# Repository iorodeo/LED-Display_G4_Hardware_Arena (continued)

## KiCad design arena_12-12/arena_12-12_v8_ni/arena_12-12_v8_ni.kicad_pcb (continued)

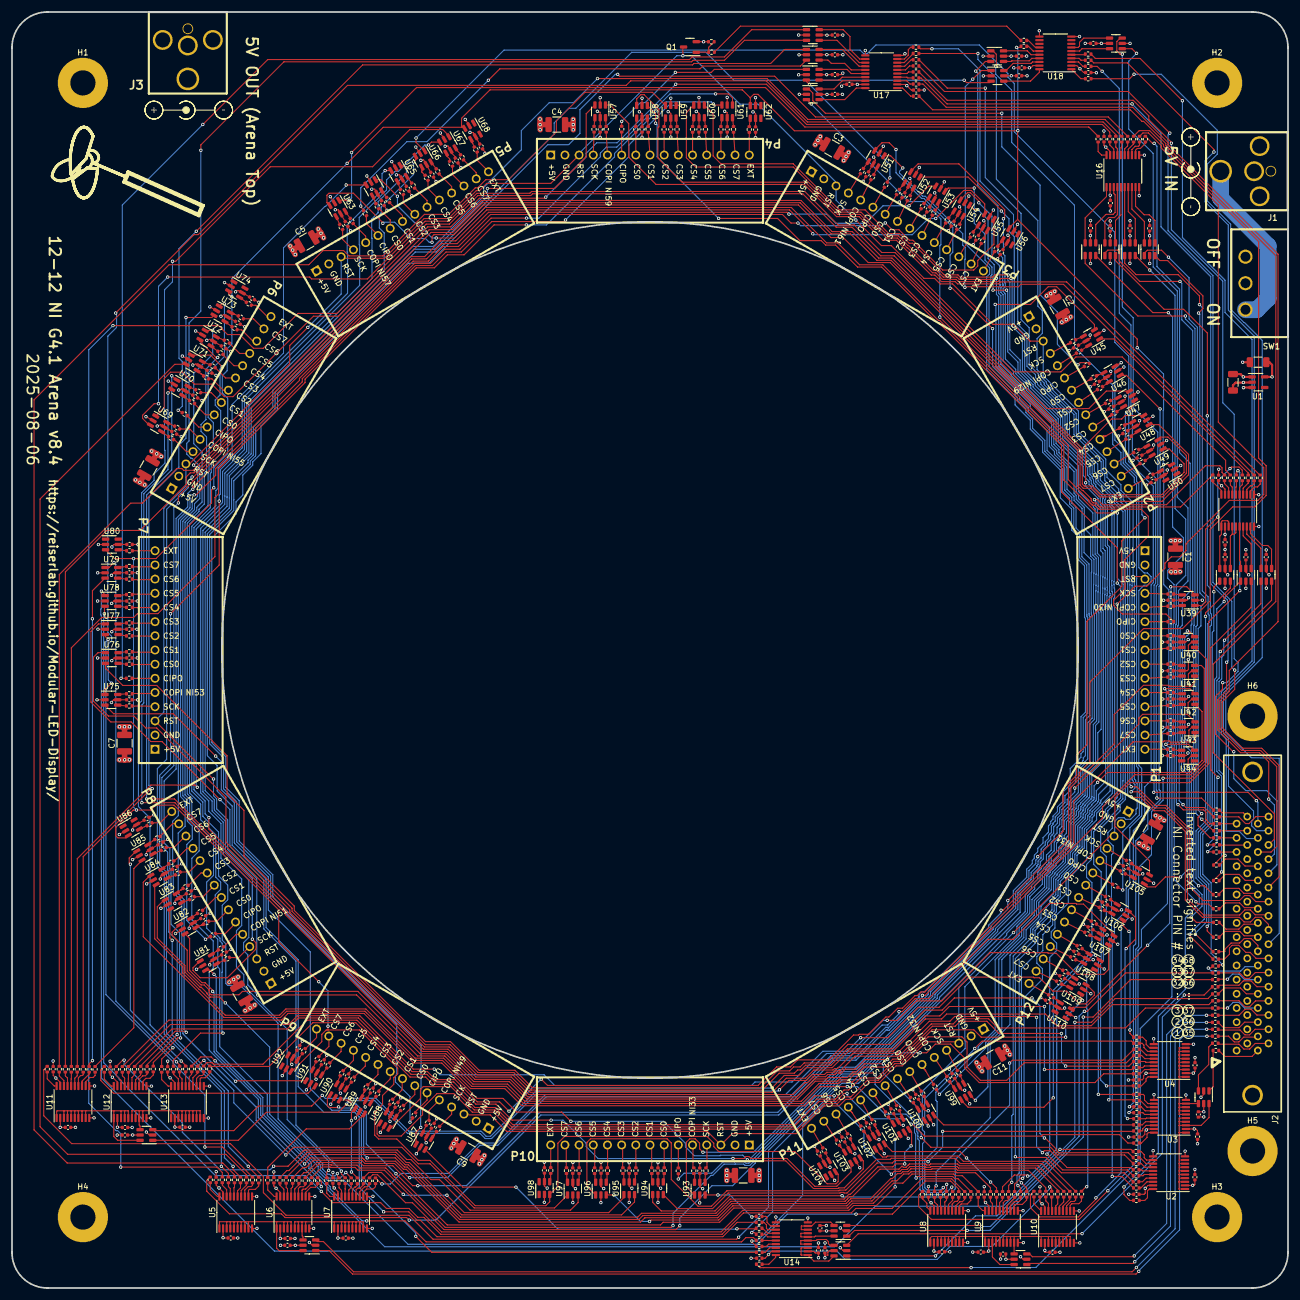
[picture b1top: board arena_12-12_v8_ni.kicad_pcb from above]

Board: 6 copper layers, 228.6 x 228.6 mm, 581 parts (0 on the bottom side), 658 nets.

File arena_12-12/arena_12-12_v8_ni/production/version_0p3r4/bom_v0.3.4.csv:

Designator,Footprint,Quantity,Value,LCSC Part #
"C1, C10, C11, C12, C2, C3, C4, C5, C6, C7, C8, C9",1210,12,100uF,C7432790
"C100, C101, C102, C103, C104, C105, C106, C107, C108, C109, C110, C111, C112, C113, C114, C115, C116, C117, C118, C119, C120, C121, C122, C123, C124, C125, C126, C127, C128, C129, C130, C131, C132, C133, C134, C135, C136, C137, C138, C139, C140, C15, C16, C17, C18, C19, C20, C21, C22, C23, C24, C25, C26, C27, C28, C29, C30, C31, C32, C33, C34, C35, C36, C37, C38, C39, C40, C41, C42, C43, C44, C45, C46, C47, C48, C49, C50, C51, C52, C53, C54, C55, C56, C57, C58, C59, C60, C61, C62, C63, C64, C65, C66, C67, C68, C69, C70, C71, C72, C73, C74, C75, C76, C77, C78, C79, C80, C81, C82, C83, C84, C85, C86, C87, C88, C89, C90, C91, C92, C93, C94, C95, C96, C97, C98, C99",0402,126,0.1uF,C1525
"C13, C14",1206,2,10uF,C342827
"J1, J3",DCJACK_2PIN_HIGHCURRENT,2,Barrel_Jack,C2928097
J2,TE_CONN_DSUB_VERT_68,1,NI_TE_68pos,C5172587
"P1, P10, P11, P12, P2, P3, P4, P5, P6, P7, P8, P9",HEADER_TOP,12,CONN15,C18078136
Q1,SOT-23-3,1,MOSFET_NCHAN,C165220
"R1, R10, R100, R101, R102, R103, R104, R105, R106, R107, R108, R109, R11, R110, R111, R112, R113, R114, R115, R116, R117, R118, R119, R12, R120, R121, R122, R123, R124, R125, R126, R127, R128, R129, R13, R130, R131, R132, R133, R134, R135, R136, R137, R138, R139, R14, R140, R141, R142, R143, R144, R145, R146, R147, R148, R149, R15, R150, R151, R152, R153, R154, R155, R156, R157, R158, R159, R16, R160, R161, R162, R163, R164, R165, R166, R167, R168, R169, R17, R170, R171, R172, R173, R174, R175, R176, R177, R178, R179, R18, R180, R181, R182, R183, R184, R185, R186, R187, R188, R189, R19, R190, R191, R192, R193, R194, R195, R196, R197, R198, R199, R2, R20, R200, R201, R202, R203, R204, R205, R206, R207, R208, R209, R21, R210, R211, R212, R213, R214, R215, R216, R217, R218, R219, R22, R220, R221, R222, R223, R224, R225, R226, R227, R228, R229, R23, R230, R231, R232, R233, R234, R235, R236, R237, R238, R239, R24, R240, R241, R242, R243, R244, R245, R246, R247, R248, R249, R25, R250, R251, R252, R253, R254, R255, R256, R257, R258, R259, R26, R260, R261, R262, R263, R264, R265, R266, R267, R268, R269, R27, R270, R271, R272, R273, R274, R275, R276, R277, R278, R279",0402,200,33,C25105
"R28, R280, R281, R282, R283, R284, R285, R286, R287, R288, R289, R29, R290, R291, R292, R293, R294, R295, R296, R297, R298, R299, R3, R30, R300, R301, R302, R303, R304, R305, R306, R31, R32, R33, R34, R35, R36, R37, R38, R39, R4, R40, R41, R42, R43, R44, R45, R46, R47, R48, R49, R5, R50, R51, R52, R53, R54, R55, R56, R57, R58, R59, R6, R60, R61, R62, R63, R64, R65, R66, R67, R68, R69, R7, R70, R71, R72, R73, R74, R75, R76, R77, R78, R79, R8, R80, R81, R82, R83, R84, R85, R86, R87, R88, R89, R9, R90, R91, R92, R93, R94, R95, R96, R97, R98, R99",0402,106,33,C25105
R307,0402,1,20k,C25765
R308,0402,1,200,C25087
SW1,slide_switch,1,SW_SPDT,C2798743
U1,SOT-23-5,1,AP2112K-3.3,C51118
"U10, U11, U12, U13, U14, U15, U16, U17, U18, U2, U3, U4, U5, U6, U7, U8, U9",TSSOP-20_4.4x6.5mm_P0.65mm,17,TXB0108PW,C53406
"U100, U101, U102, U103, U104, U105, U106, U107, U108, U109, U110, U19, U20, U21, U22, U23, U24, U25, U26, U27, U28, U29, U30, U31, U32, U33, U34, U35, U36, U37, U38, U39, U40, U41, U42, U43, U44, U45, U46, U47, U48, U49, U50, U51, U52, U53, U54, U55, U56, U57, U58, U59, U60, U61, U62, U63, U64, U65, U66, U67, U68, U69, U70, U71, U72, U73, U74, U75, U76, U77, U78, U79, U80, U81, U82, U83, U84, U85, U86, U87, U88, U89, U90, U91, U92, U93, U94, U95, U96, U97, U98, U99",SOT-23-6,92,74LVC2G17,C10429

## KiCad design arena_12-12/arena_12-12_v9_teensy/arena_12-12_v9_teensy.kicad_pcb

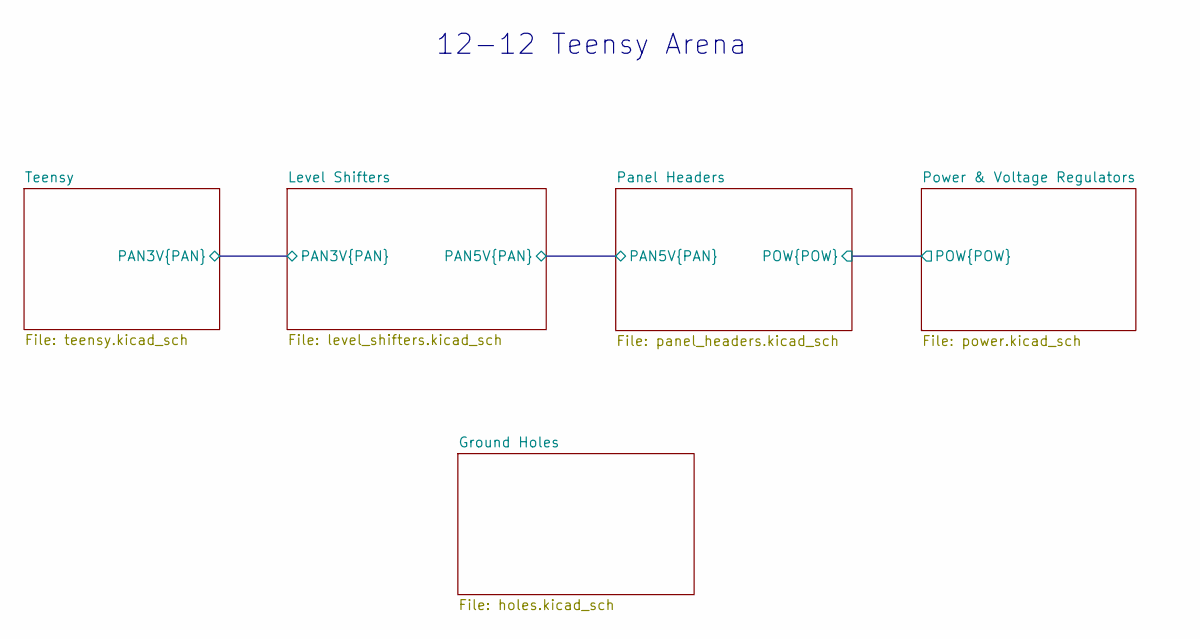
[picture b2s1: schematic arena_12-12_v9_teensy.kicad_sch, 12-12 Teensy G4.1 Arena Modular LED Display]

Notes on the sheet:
12-12 Teensy Arena

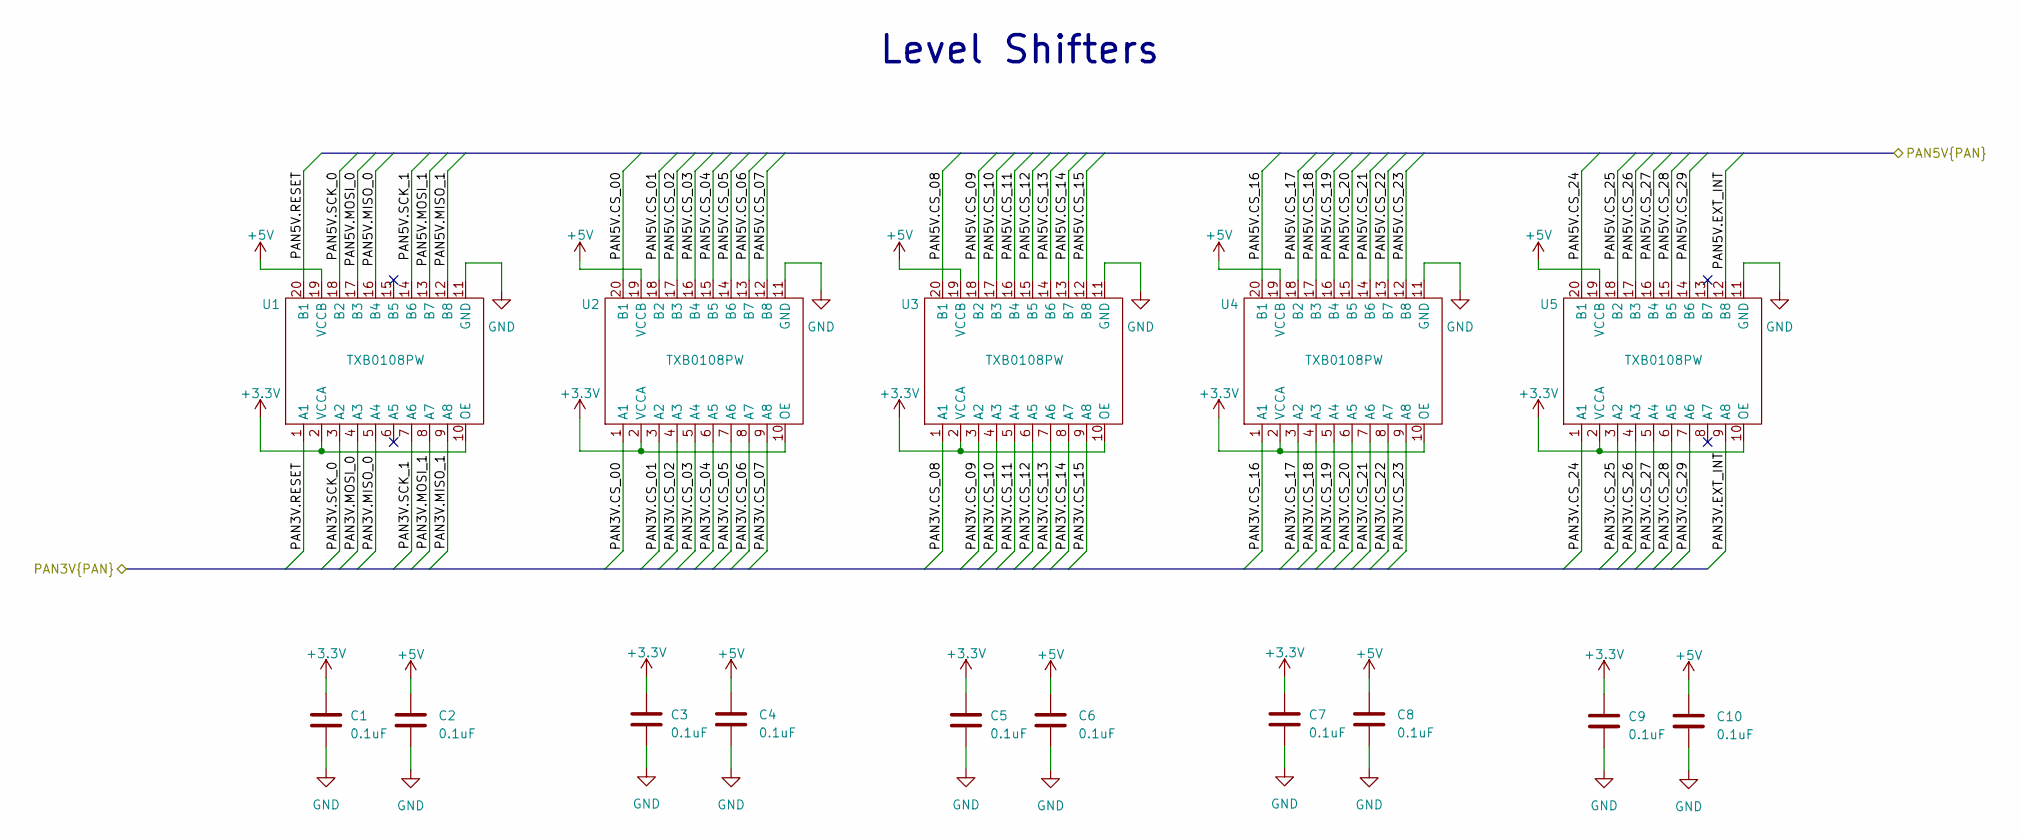
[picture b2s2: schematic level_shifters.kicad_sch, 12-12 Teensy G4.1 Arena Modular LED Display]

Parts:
C1, C2, C3, C4, C5, C6, C7, C8, C9, C10: 0.1uF; C_0603_1608Metric; MPN CL10B104KB8NNNC; DigiKey PN 1276-1000-2-ND
U1, U2, U3, U4, U5: TXB0108PW; TSSOP-20_4.4x6.5mm_P0.65mm; MPN TXB0108PWR; DigiKey PN 296-21527-2-ND

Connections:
+3.3V: C1.1, C3.1, C5.1, C7.1, C9.1, U1.2 (VCCA), U1.10 (OE), U2.2 (VCCA), U2.10 (OE), U3.2 (VCCA), U3.10 (OE), U4.2 (VCCA), U4.10 (OE), U5.2 (VCCA), U5.10 (OE); also elsewhere on the board
+5V: C2.1, C4.1, C6.1, C8.1, C10.1, U1.19 (VCCB), U2.19 (VCCB), U3.19 (VCCB), U4.19 (VCCB), U5.19 (VCCB); also elsewhere on the board
/Level Shifters/PAN3V.CS_00: U2.1 (A1); also elsewhere on the board
/Level Shifters/PAN3V.CS_01: U2.3 (A2); also elsewhere on the board
/Level Shifters/PAN3V.CS_02: U2.4 (A3); also elsewhere on the board
/Level Shifters/PAN3V.CS_03: U2.5 (A4); also elsewhere on the board
/Level Shifters/PAN3V.CS_04: U2.6 (A5); also elsewhere on the board
/Level Shifters/PAN3V.CS_05: U2.7 (A6); also elsewhere on the board
/Level Shifters/PAN3V.CS_06: U2.8 (A7); also elsewhere on the board
/Level Shifters/PAN3V.CS_07: U2.9 (A8); also elsewhere on the board
/Level Shifters/PAN3V.CS_08: U3.1 (A1); also elsewhere on the board
/Level Shifters/PAN3V.CS_09: U3.3 (A2); also elsewhere on the board
/Level Shifters/PAN3V.CS_10: U3.4 (A3); also elsewhere on the board
/Level Shifters/PAN3V.CS_11: U3.5 (A4); also elsewhere on the board
/Level Shifters/PAN3V.CS_12: U3.6 (A5); also elsewhere on the board
/Level Shifters/PAN3V.CS_13: U3.7 (A6); also elsewhere on the board
/Level Shifters/PAN3V.CS_14: U3.8 (A7); also elsewhere on the board
/Level Shifters/PAN3V.CS_15: U3.9 (A8); also elsewhere on the board
/Level Shifters/PAN3V.CS_16: U4.1 (A1); also elsewhere on the board
/Level Shifters/PAN3V.CS_17: U4.3 (A2); also elsewhere on the board
/Level Shifters/PAN3V.CS_18: U4.4 (A3); also elsewhere on the board
/Level Shifters/PAN3V.CS_19: U4.5 (A4); also elsewhere on the board
/Level Shifters/PAN3V.CS_20: U4.6 (A5); also elsewhere on the board
/Level Shifters/PAN3V.CS_21: U4.7 (A6); also elsewhere on the board
/Level Shifters/PAN3V.CS_22: U4.8 (A7); also elsewhere on the board
/Level Shifters/PAN3V.CS_23: U4.9 (A8); also elsewhere on the board
/Level Shifters/PAN3V.CS_24: U5.1 (A1); also elsewhere on the board
/Level Shifters/PAN3V.CS_25: U5.3 (A2); also elsewhere on the board
/Level Shifters/PAN3V.CS_26: U5.4 (A3); also elsewhere on the board
/Level Shifters/PAN3V.CS_27: U5.5 (A4); also elsewhere on the board
/Level Shifters/PAN3V.CS_28: U5.6 (A5); also elsewhere on the board
/Level Shifters/PAN3V.CS_29: U5.7 (A6); also elsewhere on the board
/Level Shifters/PAN3V.EXT_INT: U5.9 (A8); also elsewhere on the board
/Level Shifters/PAN3V.MISO_0: U1.5 (A4); also elsewhere on the board
/Level Shifters/PAN3V.MISO_1: U1.9 (A8); also elsewhere on the board
/Level Shifters/PAN3V.MOSI_0: U1.4 (A3); also elsewhere on the board
/Level Shifters/PAN3V.MOSI_1: U1.8 (A7); also elsewhere on the board
/Level Shifters/PAN3V.RESET: U1.1 (A1); also elsewhere on the board
/Level Shifters/PAN3V.SCK_0: U1.3 (A2); also elsewhere on the board
/Level Shifters/PAN3V.SCK_1: U1.7 (A6); also elsewhere on the board
/Level Shifters/PAN5V.CS_00: U2.20 (B1); also elsewhere on the board
/Level Shifters/PAN5V.CS_01: U2.18 (B2); also elsewhere on the board
/Level Shifters/PAN5V.CS_02: U2.17 (B3); also elsewhere on the board
/Level Shifters/PAN5V.CS_03: U2.16 (B4); also elsewhere on the board
/Level Shifters/PAN5V.CS_04: U2.15 (B5); also elsewhere on the board
/Level Shifters/PAN5V.CS_05: U2.14 (B6); also elsewhere on the board
/Level Shifters/PAN5V.CS_06: U2.13 (B7); also elsewhere on the board
/Level Shifters/PAN5V.CS_07: U2.12 (B8); also elsewhere on the board
/Level Shifters/PAN5V.CS_08: U3.20 (B1); also elsewhere on the board
/Level Shifters/PAN5V.CS_09: U3.18 (B2); also elsewhere on the board
/Level Shifters/PAN5V.CS_10: U3.17 (B3); also elsewhere on the board
/Level Shifters/PAN5V.CS_11: U3.16 (B4); also elsewhere on the board
/Level Shifters/PAN5V.CS_12: U3.15 (B5); also elsewhere on the board
/Level Shifters/PAN5V.CS_13: U3.14 (B6); also elsewhere on the board
/Level Shifters/PAN5V.CS_14: U3.13 (B7); also elsewhere on the board
/Level Shifters/PAN5V.CS_15: U3.12 (B8); also elsewhere on the board
/Level Shifters/PAN5V.CS_16: U4.20 (B1); also elsewhere on the board
/Level Shifters/PAN5V.CS_17: U4.18 (B2); also elsewhere on the board
/Level Shifters/PAN5V.CS_18: U4.17 (B3); also elsewhere on the board
/Level Shifters/PAN5V.CS_19: U4.16 (B4); also elsewhere on the board
/Level Shifters/PAN5V.CS_20: U4.15 (B5); also elsewhere on the board
/Level Shifters/PAN5V.CS_21: U4.14 (B6); also elsewhere on the board
/Level Shifters/PAN5V.CS_22: U4.13 (B7); also elsewhere on the board
/Level Shifters/PAN5V.CS_23: U4.12 (B8); also elsewhere on the board
/Level Shifters/PAN5V.CS_24: U5.20 (B1); also elsewhere on the board
/Level Shifters/PAN5V.CS_25: U5.18 (B2); also elsewhere on the board
/Level Shifters/PAN5V.CS_26: U5.17 (B3); also elsewhere on the board
/Level Shifters/PAN5V.CS_27: U5.16 (B4); also elsewhere on the board
/Level Shifters/PAN5V.CS_28: U5.15 (B5); also elsewhere on the board
/Level Shifters/PAN5V.CS_29: U5.14 (B6); also elsewhere on the board
/Level Shifters/PAN5V.EXT_INT: U5.12 (B8); also elsewhere on the board
/Level Shifters/PAN5V.MISO_0: U1.16 (B4); also elsewhere on the board
/Level Shifters/PAN5V.MISO_1: U1.12 (B8); also elsewhere on the board
/Level Shifters/PAN5V.MOSI_0: U1.17 (B3); also elsewhere on the board
/Level Shifters/PAN5V.MOSI_1: U1.13 (B7); also elsewhere on the board
/Level Shifters/PAN5V.RESET: U1.20 (B1); also elsewhere on the board
/Level Shifters/PAN5V.SCK_0: U1.18 (B2); also elsewhere on the board
/Level Shifters/PAN5V.SCK_1: U1.14 (B6); also elsewhere on the board
GND: C1.2, C2.2, C3.2, C4.2, C5.2, C6.2, C7.2, C8.2, C9.2, C10.2, U1.11 (GND), U2.11 (GND), U3.11 (GND), U4.11 (GND), U5.11 (GND); also elsewhere on the board

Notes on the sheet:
Level Shifters

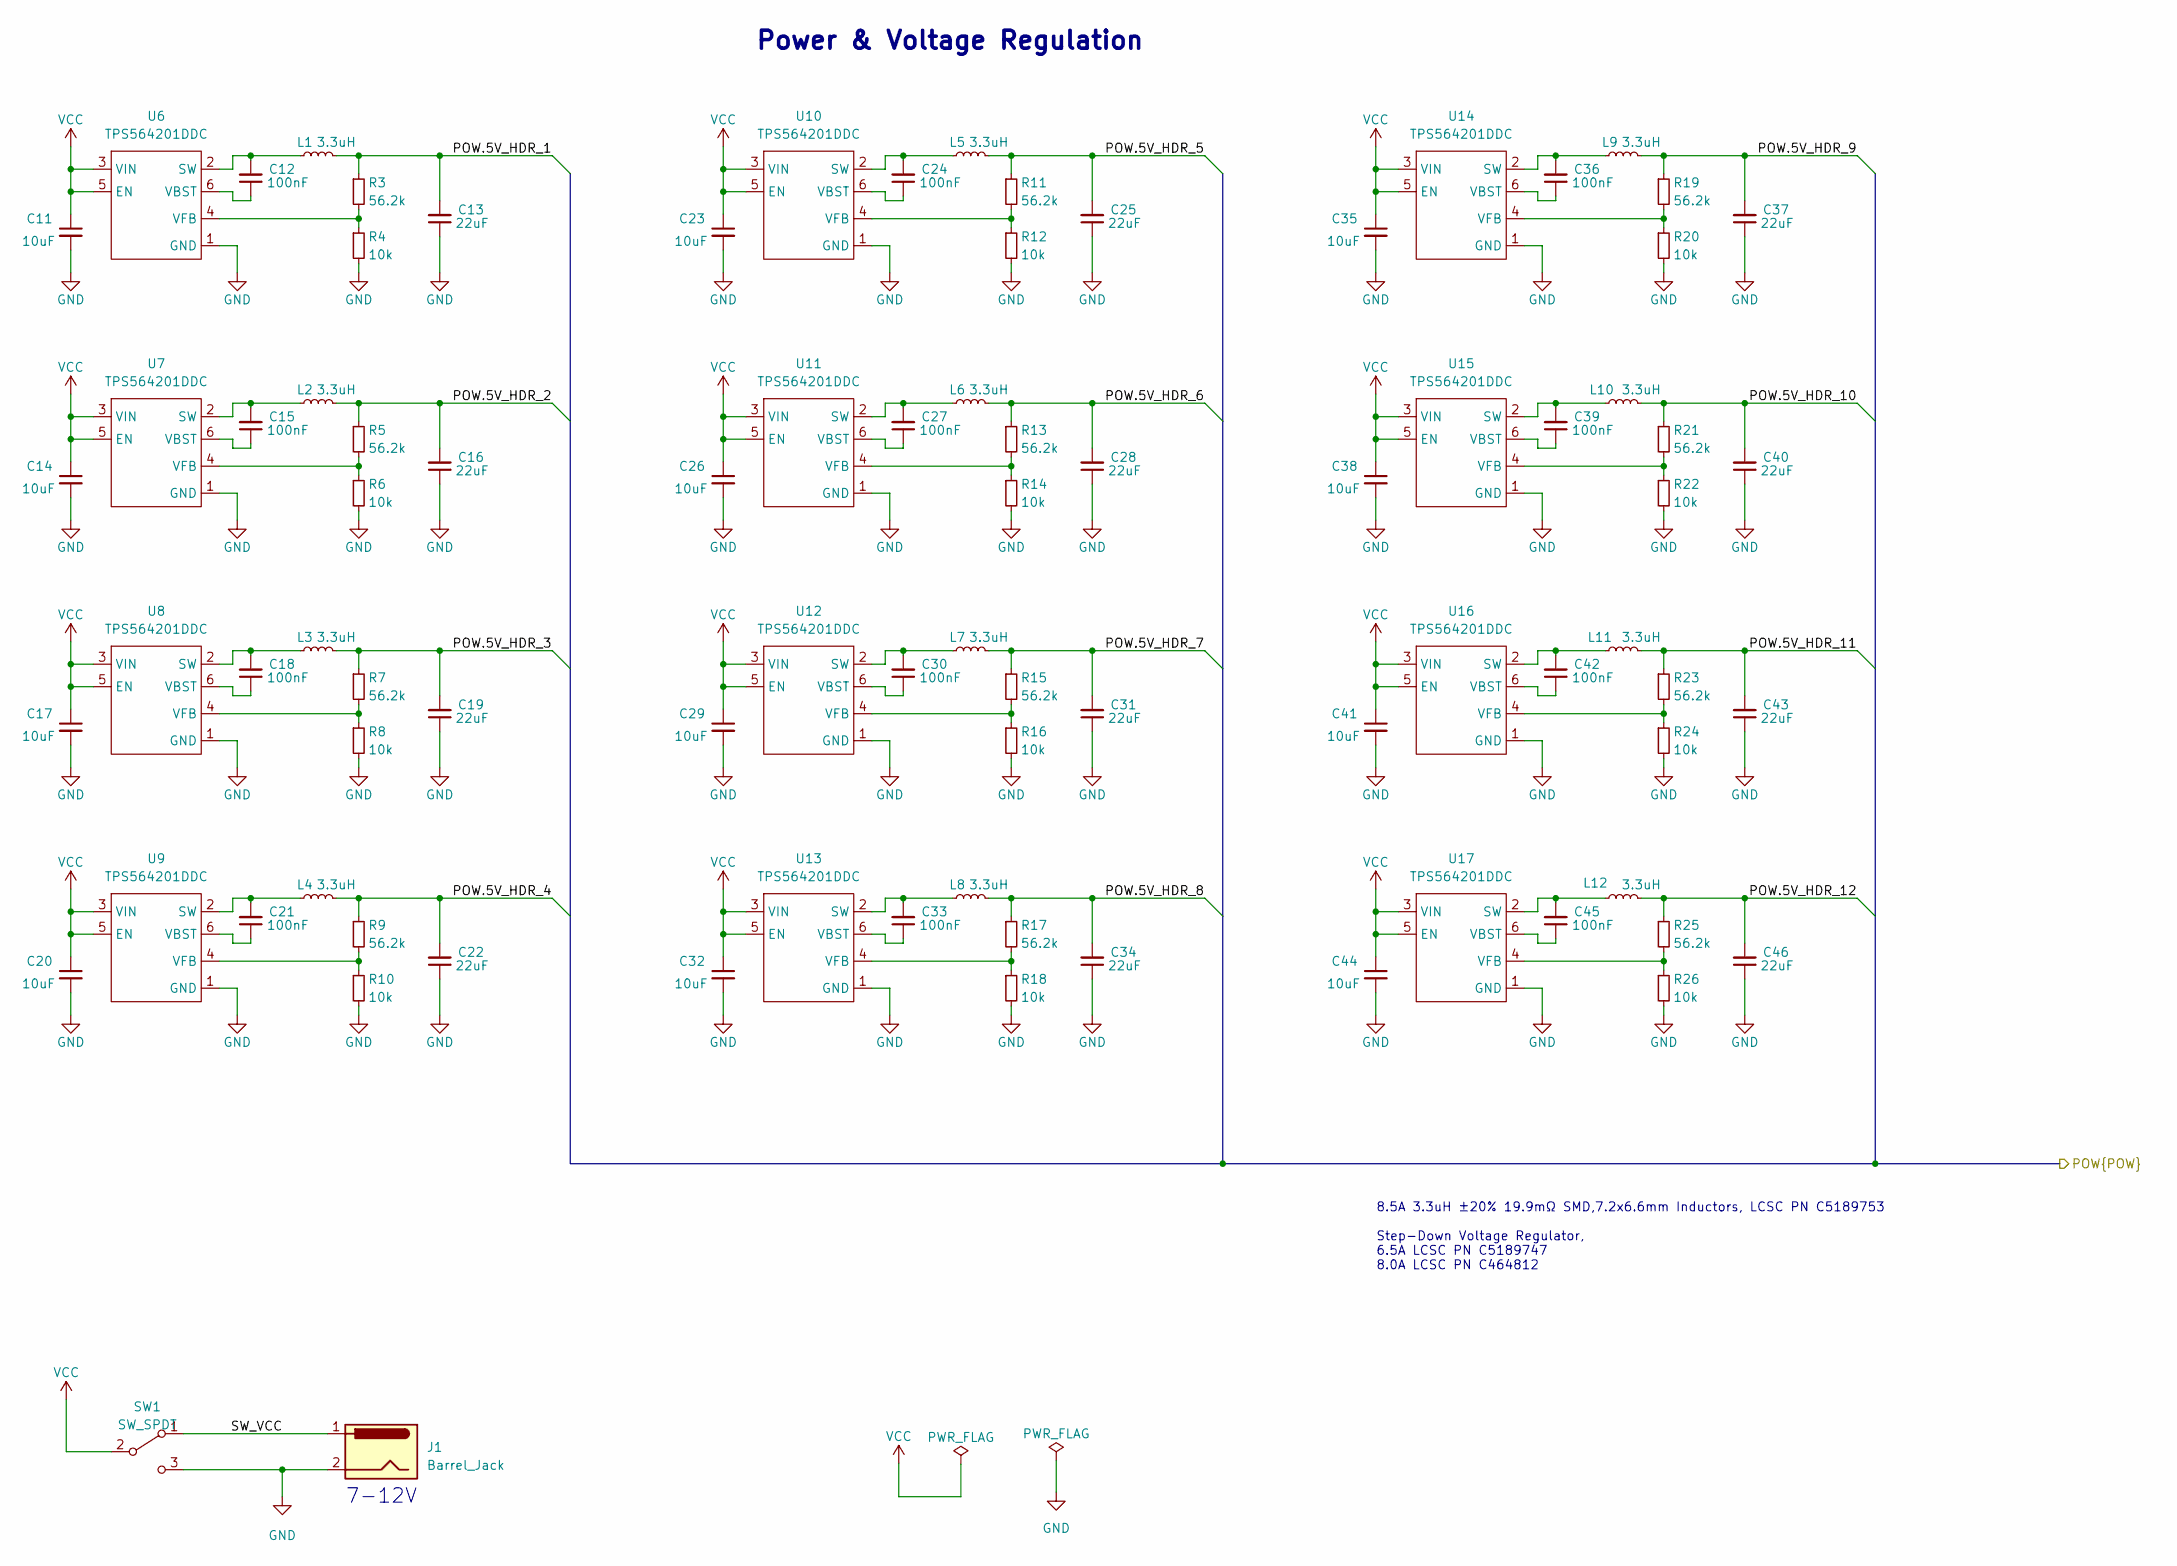
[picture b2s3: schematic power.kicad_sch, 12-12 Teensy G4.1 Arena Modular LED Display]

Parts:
C11, C14, C17, C20, C23, C26, C29, C32, C35, C38, C41, C44: 10uF; C_0603_1608Metric; MPN CL10A106MA8NRNC; DigiKey PN 1276-1869-2-ND
C12, C15, C18, C21, C24, C27, C30, C33, C36, C39, C42, C45: 100nF; C_0603_1608Metric; MPN CL10B104KB8NNNC; DigiKey PN 1276-1000-2-ND
C13, C16, C19, C22, C25, C28, C31, C34, C37, C40, C43, C46: 22uF; C_0603_1608Metric; MPN CL10A226MO7JZNC; DigiKey PN 1276-7076-2-ND
J1: Barrel_Jack; DCJACK_2PIN_HIGHCURRENT; MPN PJ-063AH; DigiKey PN CP-063AH-ND
L1, L2, L3, L4, L5, L6, L7, L8, L9, L10, L11, L12: 3.3uH; CYA0650_3P3UH; MPN CYA0630-3.3UH; LCSC PN C5189747
R3, R5, R7, R9, R11, R13, R15, R17, R19, R21, R23, R25: 56.2k; R_0603_1608Metric; MPN RT0603BRD0756K2L; DigiKey PN YAG4575TR-ND
R4, R6, R8, R10, R12, R14, R16, R18, R20, R22, R24, R26: 10k; R_0603_1608Metric; MPN RT0603BRD0710KL; DigiKey PN YAG1236TR-ND
SW1: SW_SPDT; slide_switch; MPN L102021ML04Q; DigiKey PN CKC5102-ND
U6, U7, U8, U9, U10, U11, U12, U13, U14, U15, U16, U17: TPS564201DDC; SOT-23-6; MPN TPS564201DDCR; DigiKey PN 296-47373-2-ND

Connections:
/Panel Headers/POW.5V_HDR_1: C13.2, L1.2, R3.1; also elsewhere on the board
/Panel Headers/POW.5V_HDR_2: C16.2, L2.2, R5.1; also elsewhere on the board
/Panel Headers/POW.5V_HDR_3: C19.2, L3.2, R7.1; also elsewhere on the board
/Panel Headers/POW.5V_HDR_4: C22.2, L4.2, R9.1; also elsewhere on the board
/Panel Headers/POW.5V_HDR_5: C25.2, L5.2, R11.1; also elsewhere on the board
/Panel Headers/POW.5V_HDR_6: C28.2, L6.2, R13.1; also elsewhere on the board
/Panel Headers/POW.5V_HDR_7: C31.2, L7.2, R15.1; also elsewhere on the board
/Panel Headers/POW.5V_HDR_8: C34.2, L8.2, R17.1; also elsewhere on the board
/Panel Headers/POW.5V_HDR_9: C37.2, L9.2, R19.1; also elsewhere on the board
/Panel Headers/POW.5V_HDR_10: C40.2, L10.2, R21.1; also elsewhere on the board
/Panel Headers/POW.5V_HDR_11: C43.2, L11.2, R23.1; also elsewhere on the board
/Panel Headers/POW.5V_HDR_12: C46.2, L12.2, R25.1; also elsewhere on the board
/Power & Voltage Regulators/SW_VCC: J1.1, SW1.1 (A)
GND: C11.2, C13.1, C14.2, C16.1, C17.2, C19.1, C20.2, C22.1, C23.2, C25.1, C26.2, C28.1, C29.2, C31.1, C32.2, C34.1, C35.2, C37.1, C38.2, C40.1, C41.2, C43.1, C44.2, C46.1, J1.2, R4.2, R6.2, R8.2, R10.2, R12.2, R14.2, R16.2, R18.2, R20.2, R22.2, R24.2, R26.2, SW1.3 (C), U6.1 (GND), U7.1 (GND), U8.1 (GND), U9.1 (GND), U10.1 (GND), U11.1 (GND), U12.1 (GND), U13.1 (GND), U14.1 (GND), U15.1 (GND), U16.1 (GND), U17.1 (GND); also elsewhere on the board
unnamed: C12.2, L1.1, U6.2 (SW)
unnamed: C12.1, U6.6 (VBST)
unnamed: R3.2, R4.1, U6.4 (VFB)
unnamed: C15.2, L2.1, U7.2 (SW)
unnamed: C15.1, U7.6 (VBST)
unnamed: R5.2, R6.1, U7.4 (VFB)
unnamed: C18.2, L3.1, U8.2 (SW)
unnamed: C18.1, U8.6 (VBST)
unnamed: R7.2, R8.1, U8.4 (VFB)
unnamed: C21.2, L4.1, U9.2 (SW)
unnamed: C21.1, U9.6 (VBST)
unnamed: R9.2, R10.1, U9.4 (VFB)
unnamed: C24.2, L5.1, U10.2 (SW)
unnamed: C24.1, U10.6 (VBST)
unnamed: R11.2, R12.1, U10.4 (VFB)
unnamed: C27.2, L6.1, U11.2 (SW)
unnamed: C27.1, U11.6 (VBST)
unnamed: R13.2, R14.1, U11.4 (VFB)
unnamed: C30.2, L7.1, U12.2 (SW)
unnamed: C30.1, U12.6 (VBST)
unnamed: R15.2, R16.1, U12.4 (VFB)
unnamed: C33.2, L8.1, U13.2 (SW)
unnamed: C33.1, U13.6 (VBST)
unnamed: R17.2, R18.1, U13.4 (VFB)
unnamed: C36.2, L9.1, U14.2 (SW)
unnamed: C36.1, U14.6 (VBST)
unnamed: R19.2, R20.1, U14.4 (VFB)
unnamed: C39.2, L10.1, U15.2 (SW)
unnamed: C39.1, U15.6 (VBST)
unnamed: R21.2, R22.1, U15.4 (VFB)
unnamed: C42.2, L11.1, U16.2 (SW)
unnamed: C42.1, U16.6 (VBST)
unnamed: R23.2, R24.1, U16.4 (VFB)
unnamed: C45.2, L12.1, U17.2 (SW)
unnamed: C45.1, U17.6 (VBST)
unnamed: R25.2, R26.1, U17.4 (VFB)
VCC: C11.1, C14.1, C17.1, C20.1, C23.1, C26.1, C29.1, C32.1, C35.1, C38.1, C41.1, C44.1, SW1.2 (B), U6.3 (VIN), U6.5 (EN), U7.3 (VIN), U7.5 (EN), U8.3 (VIN), U8.5 (EN), U9.3 (VIN), U9.5 (EN), U10.3 (VIN), U10.5 (EN), U11.3 (VIN), U11.5 (EN), U12.3 (VIN), U12.5 (EN), U13.3 (VIN), U13.5 (EN), U14.3 (VIN), U14.5 (EN), U15.3 (VIN), U15.5 (EN), U16.3 (VIN), U16.5 (EN), U17.3 (VIN), U17.5 (EN)

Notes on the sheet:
7-12V
8.5A 3.3uH ±20% 19.9mΩ SMD,7.2x6.6mm Inductors, LCSC PN C5189753 Step-Down Voltage Regulator, 6.5A LCSC PN C5189747 8.0A LCSC PN C464812
Power & Voltage Regulation

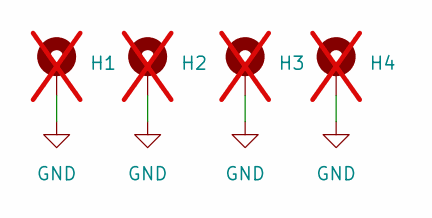
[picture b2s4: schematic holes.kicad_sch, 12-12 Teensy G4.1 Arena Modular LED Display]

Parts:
H1, H2, H3, H4: MountingHole_Pad; MountingHole_4.5mm_Pad; not fitted

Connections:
GND: H1.1, H2.1, H3.1, H4.1; also elsewhere on the board

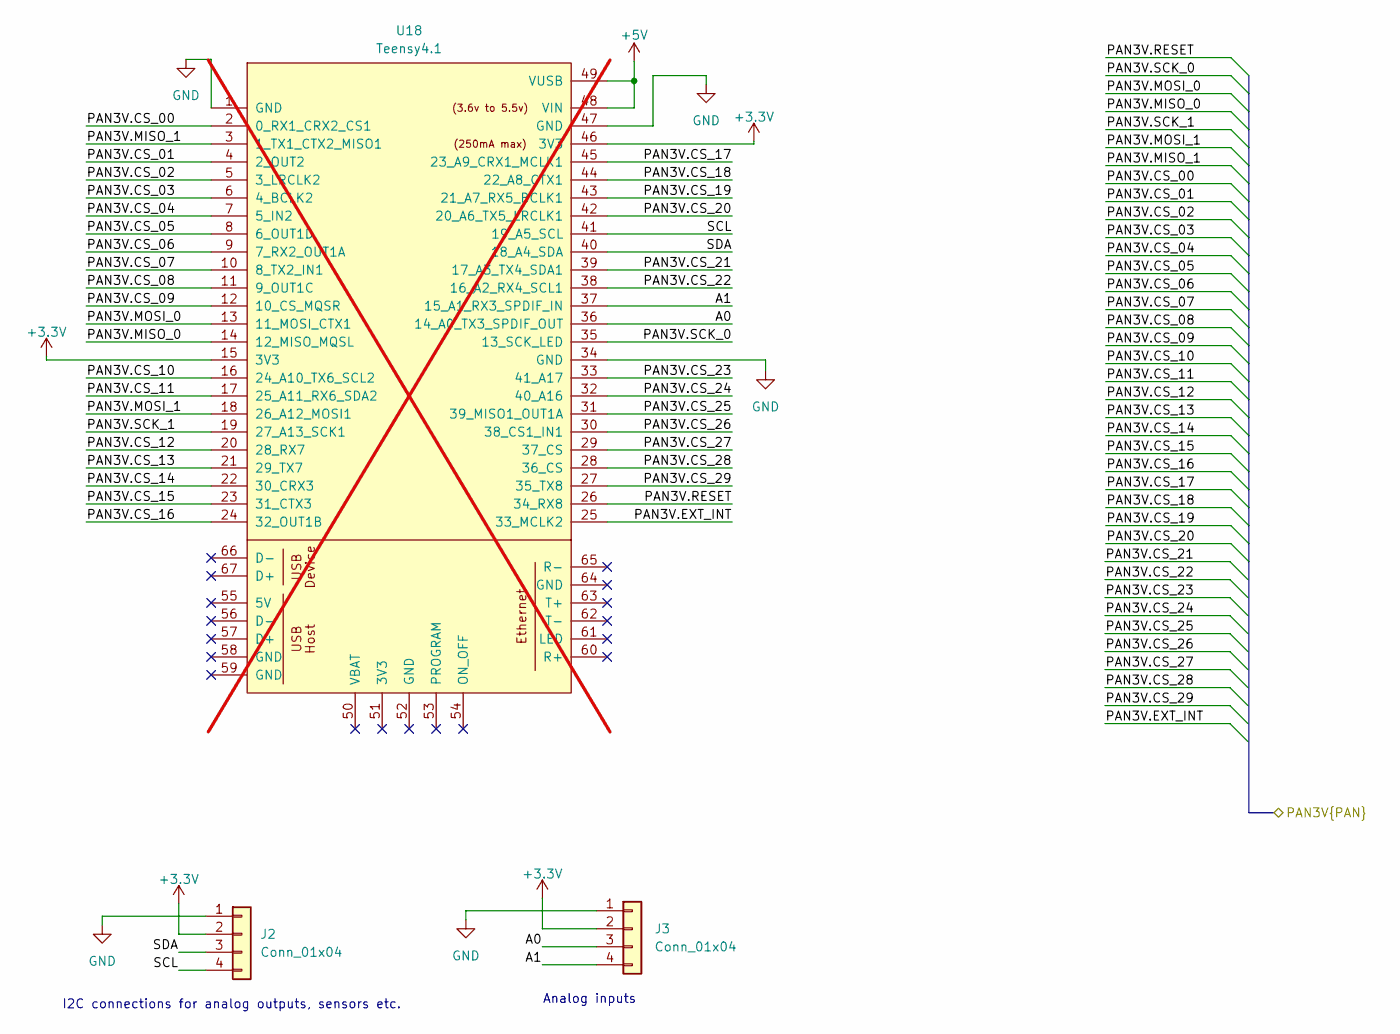
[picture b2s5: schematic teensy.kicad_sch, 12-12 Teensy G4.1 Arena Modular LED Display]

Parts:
J2, J3: Conn_01x04; JST_SH_SM04B-SRSS-TB_1x04-1MP_P1.00mm_Horizontal; MPN 1.0T-4P; LCSC PN C145956
U18: Teensy4.1; Teensy41; not fitted

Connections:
+3.3V: J2.2, J3.2, U18.15 (3V3), U18.46 (3V3); also elsewhere on the board
+5V: U18.48 (VIN), U18.49 (VUSB); also elsewhere on the board
/Level Shifters/PAN3V.CS_00: U18.2 (0_RX1_CRX2_CS1); also elsewhere on the board
/Level Shifters/PAN3V.CS_01: U18.4 (2_OUT2); also elsewhere on the board
/Level Shifters/PAN3V.CS_02: U18.5 (3_LRCLK2); also elsewhere on the board
/Level Shifters/PAN3V.CS_03: U18.6 (4_BCLK2); also elsewhere on the board
/Level Shifters/PAN3V.CS_04: U18.7 (5_IN2); also elsewhere on the board
/Level Shifters/PAN3V.CS_05: U18.8 (6_OUT1D); also elsewhere on the board
/Level Shifters/PAN3V.CS_06: U18.9 (7_RX2_OUT1A); also elsewhere on the board
/Level Shifters/PAN3V.CS_07: U18.10 (8_TX2_IN1); also elsewhere on the board
/Level Shifters/PAN3V.CS_08: U18.11 (9_OUT1C); also elsewhere on the board
/Level Shifters/PAN3V.CS_09: U18.12 (10_CS_MQSR); also elsewhere on the board
/Level Shifters/PAN3V.CS_10: U18.16 (24_A10_TX6_SCL2); also elsewhere on the board
/Level Shifters/PAN3V.CS_11: U18.17 (25_A11_RX6_SDA2); also elsewhere on the board
/Level Shifters/PAN3V.CS_12: U18.20 (28_RX7); also elsewhere on the board
/Level Shifters/PAN3V.CS_13: U18.21 (29_TX7); also elsewhere on the board
/Level Shifters/PAN3V.CS_14: U18.22 (30_CRX3); also elsewhere on the board
/Level Shifters/PAN3V.CS_15: U18.23 (31_CTX3); also elsewhere on the board
/Level Shifters/PAN3V.CS_16: U18.24 (32_OUT1B); also elsewhere on the board
/Level Shifters/PAN3V.CS_17: U18.45 (23_A9_CRX1_MCLK1); also elsewhere on the board
/Level Shifters/PAN3V.CS_18: U18.44 (22_A8_CTX1); also elsewhere on the board
/Level Shifters/PAN3V.CS_19: U18.43 (21_A7_RX5_BCLK1); also elsewhere on the board
/Level Shifters/PAN3V.CS_20: U18.42 (20_A6_TX5_LRCLK1); also elsewhere on the board
/Level Shifters/PAN3V.CS_21: U18.39 (17_A3_TX4_SDA1); also elsewhere on the board
/Level Shifters/PAN3V.CS_22: U18.38 (16_A2_RX4_SCL1); also elsewhere on the board
/Level Shifters/PAN3V.CS_23: U18.33 (41_A17); also elsewhere on the board
/Level Shifters/PAN3V.CS_24: U18.32 (40_A16); also elsewhere on the board
/Level Shifters/PAN3V.CS_25: U18.31 (39_MISO1_OUT1A); also elsewhere on the board
/Level Shifters/PAN3V.CS_26: U18.30 (38_CS1_IN1); also elsewhere on the board
/Level Shifters/PAN3V.CS_27: U18.29 (37_CS); also elsewhere on the board
/Level Shifters/PAN3V.CS_28: U18.28 (36_CS); also elsewhere on the board
/Level Shifters/PAN3V.CS_29: U18.27 (35_TX8); also elsewhere on the board
/Level Shifters/PAN3V.EXT_INT: U18.25 (33_MCLK2); also elsewhere on the board
/Level Shifters/PAN3V.MISO_0: U18.14 (12_MISO_MQSL); also elsewhere on the board
/Level Shifters/PAN3V.MISO_1: U18.3 (1_TX1_CTX2_MISO1); also elsewhere on the board
/Level Shifters/PAN3V.MOSI_0: U18.13 (11_MOSI_CTX1); also elsewhere on the board
/Level Shifters/PAN3V.MOSI_1: U18.18 (26_A12_MOSI1); also elsewhere on the board
/Level Shifters/PAN3V.RESET: U18.26 (34_RX8); also elsewhere on the board
/Level Shifters/PAN3V.SCK_0: U18.35 (13_SCK_LED); also elsewhere on the board
/Level Shifters/PAN3V.SCK_1: U18.19 (27_A13_SCK1); also elsewhere on the board
/Teensy/A0: J3.3, U18.36 (14_A0_TX3_SPDIF_OUT)
/Teensy/A1: J3.4, U18.37 (15_A1_RX3_SPDIF_IN)
/Teensy/SCL: J2.4, U18.41 (19_A5_SCL)
/Teensy/SDA: J2.3, U18.40 (18_A4_SDA)
GND: J2.1, J3.1, U18.1 (GND), U18.34 (GND), U18.47 (GND); also elsewhere on the board

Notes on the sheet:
Analog inputs
I2C connections for analog outputs, sensors etc.
